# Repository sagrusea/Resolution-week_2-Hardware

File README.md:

# An astable vibrator in the shape of a sand clock
I made this for resolution hardware week 2. It has 8 leds 4 on each half to mimick the real life clock.
  
---
### Simulation
#### how it works
The transistors are the switches, and before that switch can turn on the led the capacitor has to charge up, when it does it puts enough current to turn the led on and also begin charging the next cap to form a loop.

[link to the sim](https://is.gd/97cx6k)
### Schematic

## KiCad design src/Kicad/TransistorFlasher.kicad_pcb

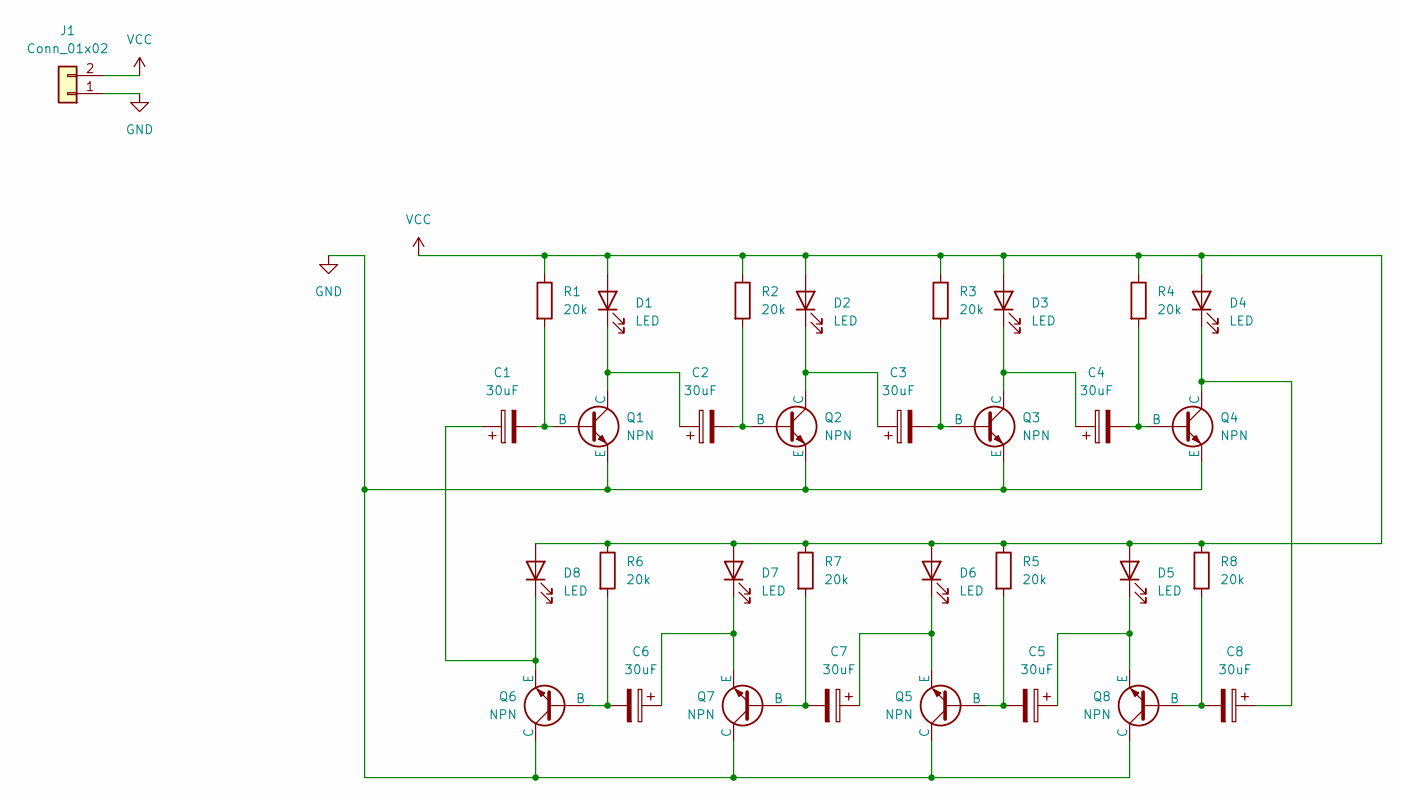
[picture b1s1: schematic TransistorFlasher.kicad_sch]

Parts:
C1, C2, C3, C4, C5, C6, C7, C8: 30uF; C_Disc_D5.0mm_W2.5mm_P5.00mm
D1, D2, D3, D4, D5, D6, D7, D8: LED; LED_D5.0mm
J1: Conn_01x02; PinHeader_1x02_P2.54mm_Vertical
Q1, Q2, Q3, Q4, Q5, Q6, Q7, Q8: NPN; TO-92L_Inline_Wide
R1, R2, R3, R4, R5, R6, R7, R8: 20k; R_Axial_DIN0204_L3.6mm_D1.6mm_P7.62mm_Horizontal

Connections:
GND: J1.1, Q1.3 (E), Q2.3 (E), Q3.3 (E), Q4.3 (E), Q5.1 (C), Q6.1 (C), Q7.1 (C), Q8.1 (C)
unnamed: C2.1, D1.1 (K), Q1.1 (C)
unnamed: C3.1, D2.1 (K), Q2.1 (C)
unnamed: C4.1, D3.1 (K), Q3.1 (C)
unnamed: C8.1, D4.1 (K), Q4.1 (C)
unnamed: C5.1, D5.1 (K), Q8.3 (E)
unnamed: C7.1, D6.1 (K), Q5.3 (E)
unnamed: C6.1, D7.1 (K), Q7.3 (E)
unnamed: C1.1, D8.1 (K), Q6.3 (E)
unnamed: C1.2, Q1.2 (B), R1.2
unnamed: C2.2, Q2.2 (B), R2.2
unnamed: C3.2, Q3.2 (B), R3.2
unnamed: C4.2, Q4.2 (B), R4.2
unnamed: C5.2, Q5.2 (B), R5.2
unnamed: C6.2, Q6.2 (B), R6.2
unnamed: C7.2, Q7.2 (B), R7.2
unnamed: C8.2, Q8.2 (B), R8.2
VCC: D1.2 (A), D2.2 (A), D3.2 (A), D4.2 (A), D5.2 (A), D6.2 (A), D7.2 (A), D8.2 (A), J1.2, R1.1, R2.1, R3.1, R4.1, R5.1, R6.1, R7.1, R8.1

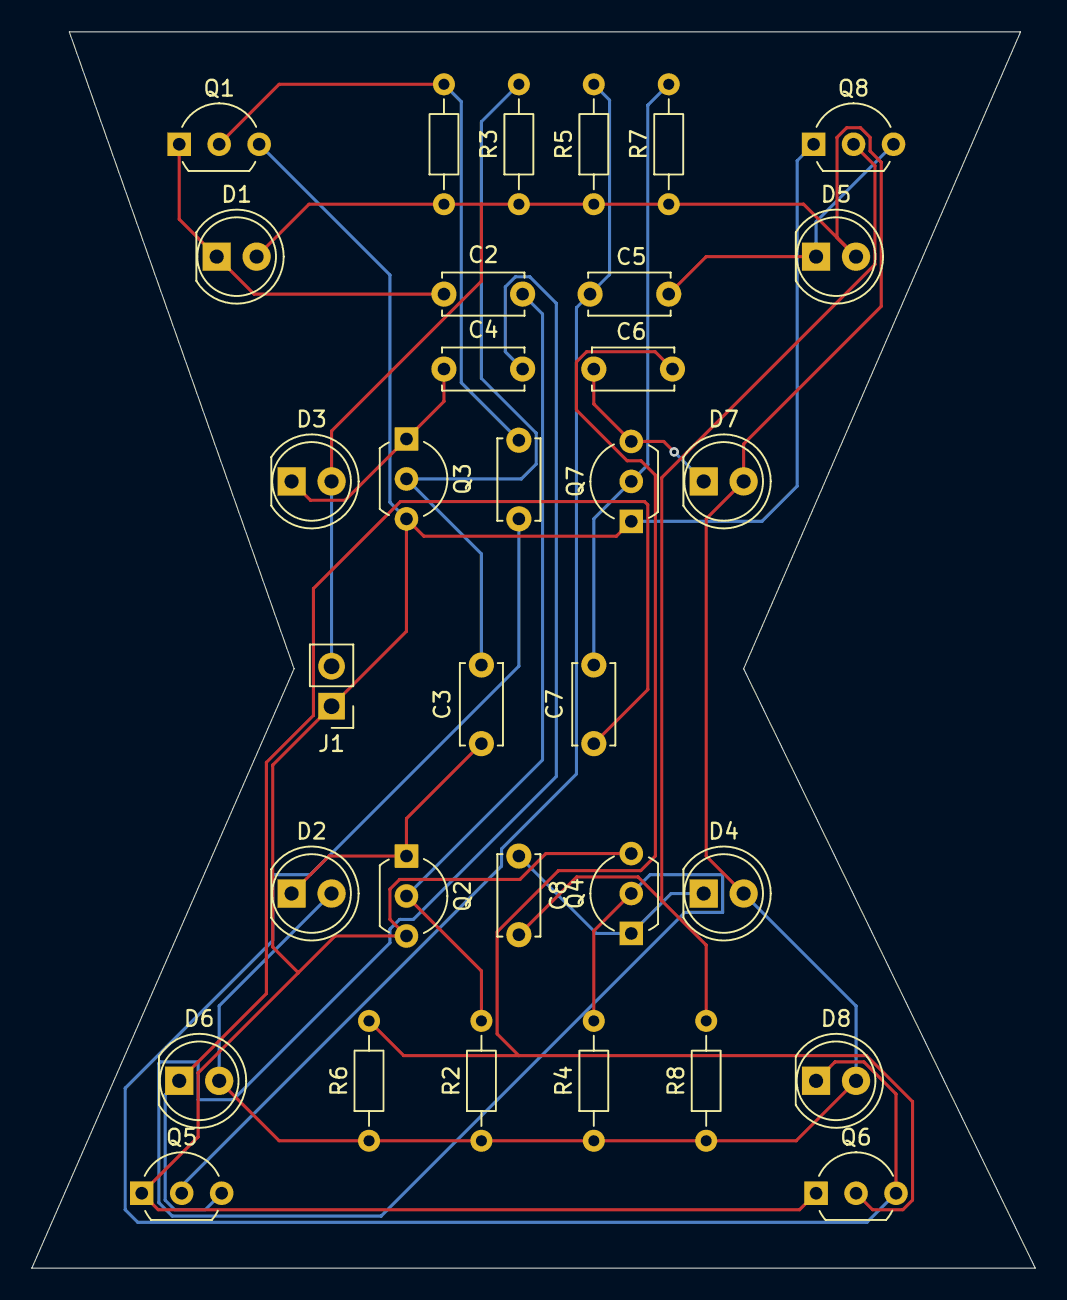
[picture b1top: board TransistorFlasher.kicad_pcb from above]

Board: 2 copper layers, 63.8 x 78.6 mm, 33 parts (0 on the bottom side), 18 nets.

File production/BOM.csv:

"Reference","Qty","Value","DNP","Exclude from BOM","Exclude from Board","Footprint","Datasheet"
"C1,C2,C3,C4,C5,C6,C7,C8","8","30uF","","","","Capacitor_THT:C_Disc_D5.0mm_W2.5mm_P5.00mm","~"
"D1,D2,D3,D4,D5,D6,D7,D8","8","LED","","","","LED_THT:LED_D5.0mm","~"
"J1","1","Conn_01x02","","","","Connector_PinHeader_2.54mm:PinHeader_1x02_P2.54mm_Vertical","~"
"Q1,Q2,Q3,Q4,Q5,Q6,Q7,Q8","8","NPN","","","","Package_TO_SOT_THT:TO-92L_Inline_Wide","https://ngspice.sourceforge.io/docs/ngspice-html-manual/manu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"
"R1,R2,R3,R4,R5,R6,R7,R8","8","20k","","","","Resistor_THT:R_Axial_DIN0204_L3.6mm_D1.6mm_P7.62mm_Horizontal","~"

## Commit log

2026-03-25 Add Transistor Flasher PCB, BOM and assets
    Add a complete KiCad project for the Transistor Flasher (PCB, schematic, .pro and lock files) along with production outputs and supporting assets. Included: PCB file (TransistorFlasher.kicad_pcb), sc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
2026-03-25 finished readme
